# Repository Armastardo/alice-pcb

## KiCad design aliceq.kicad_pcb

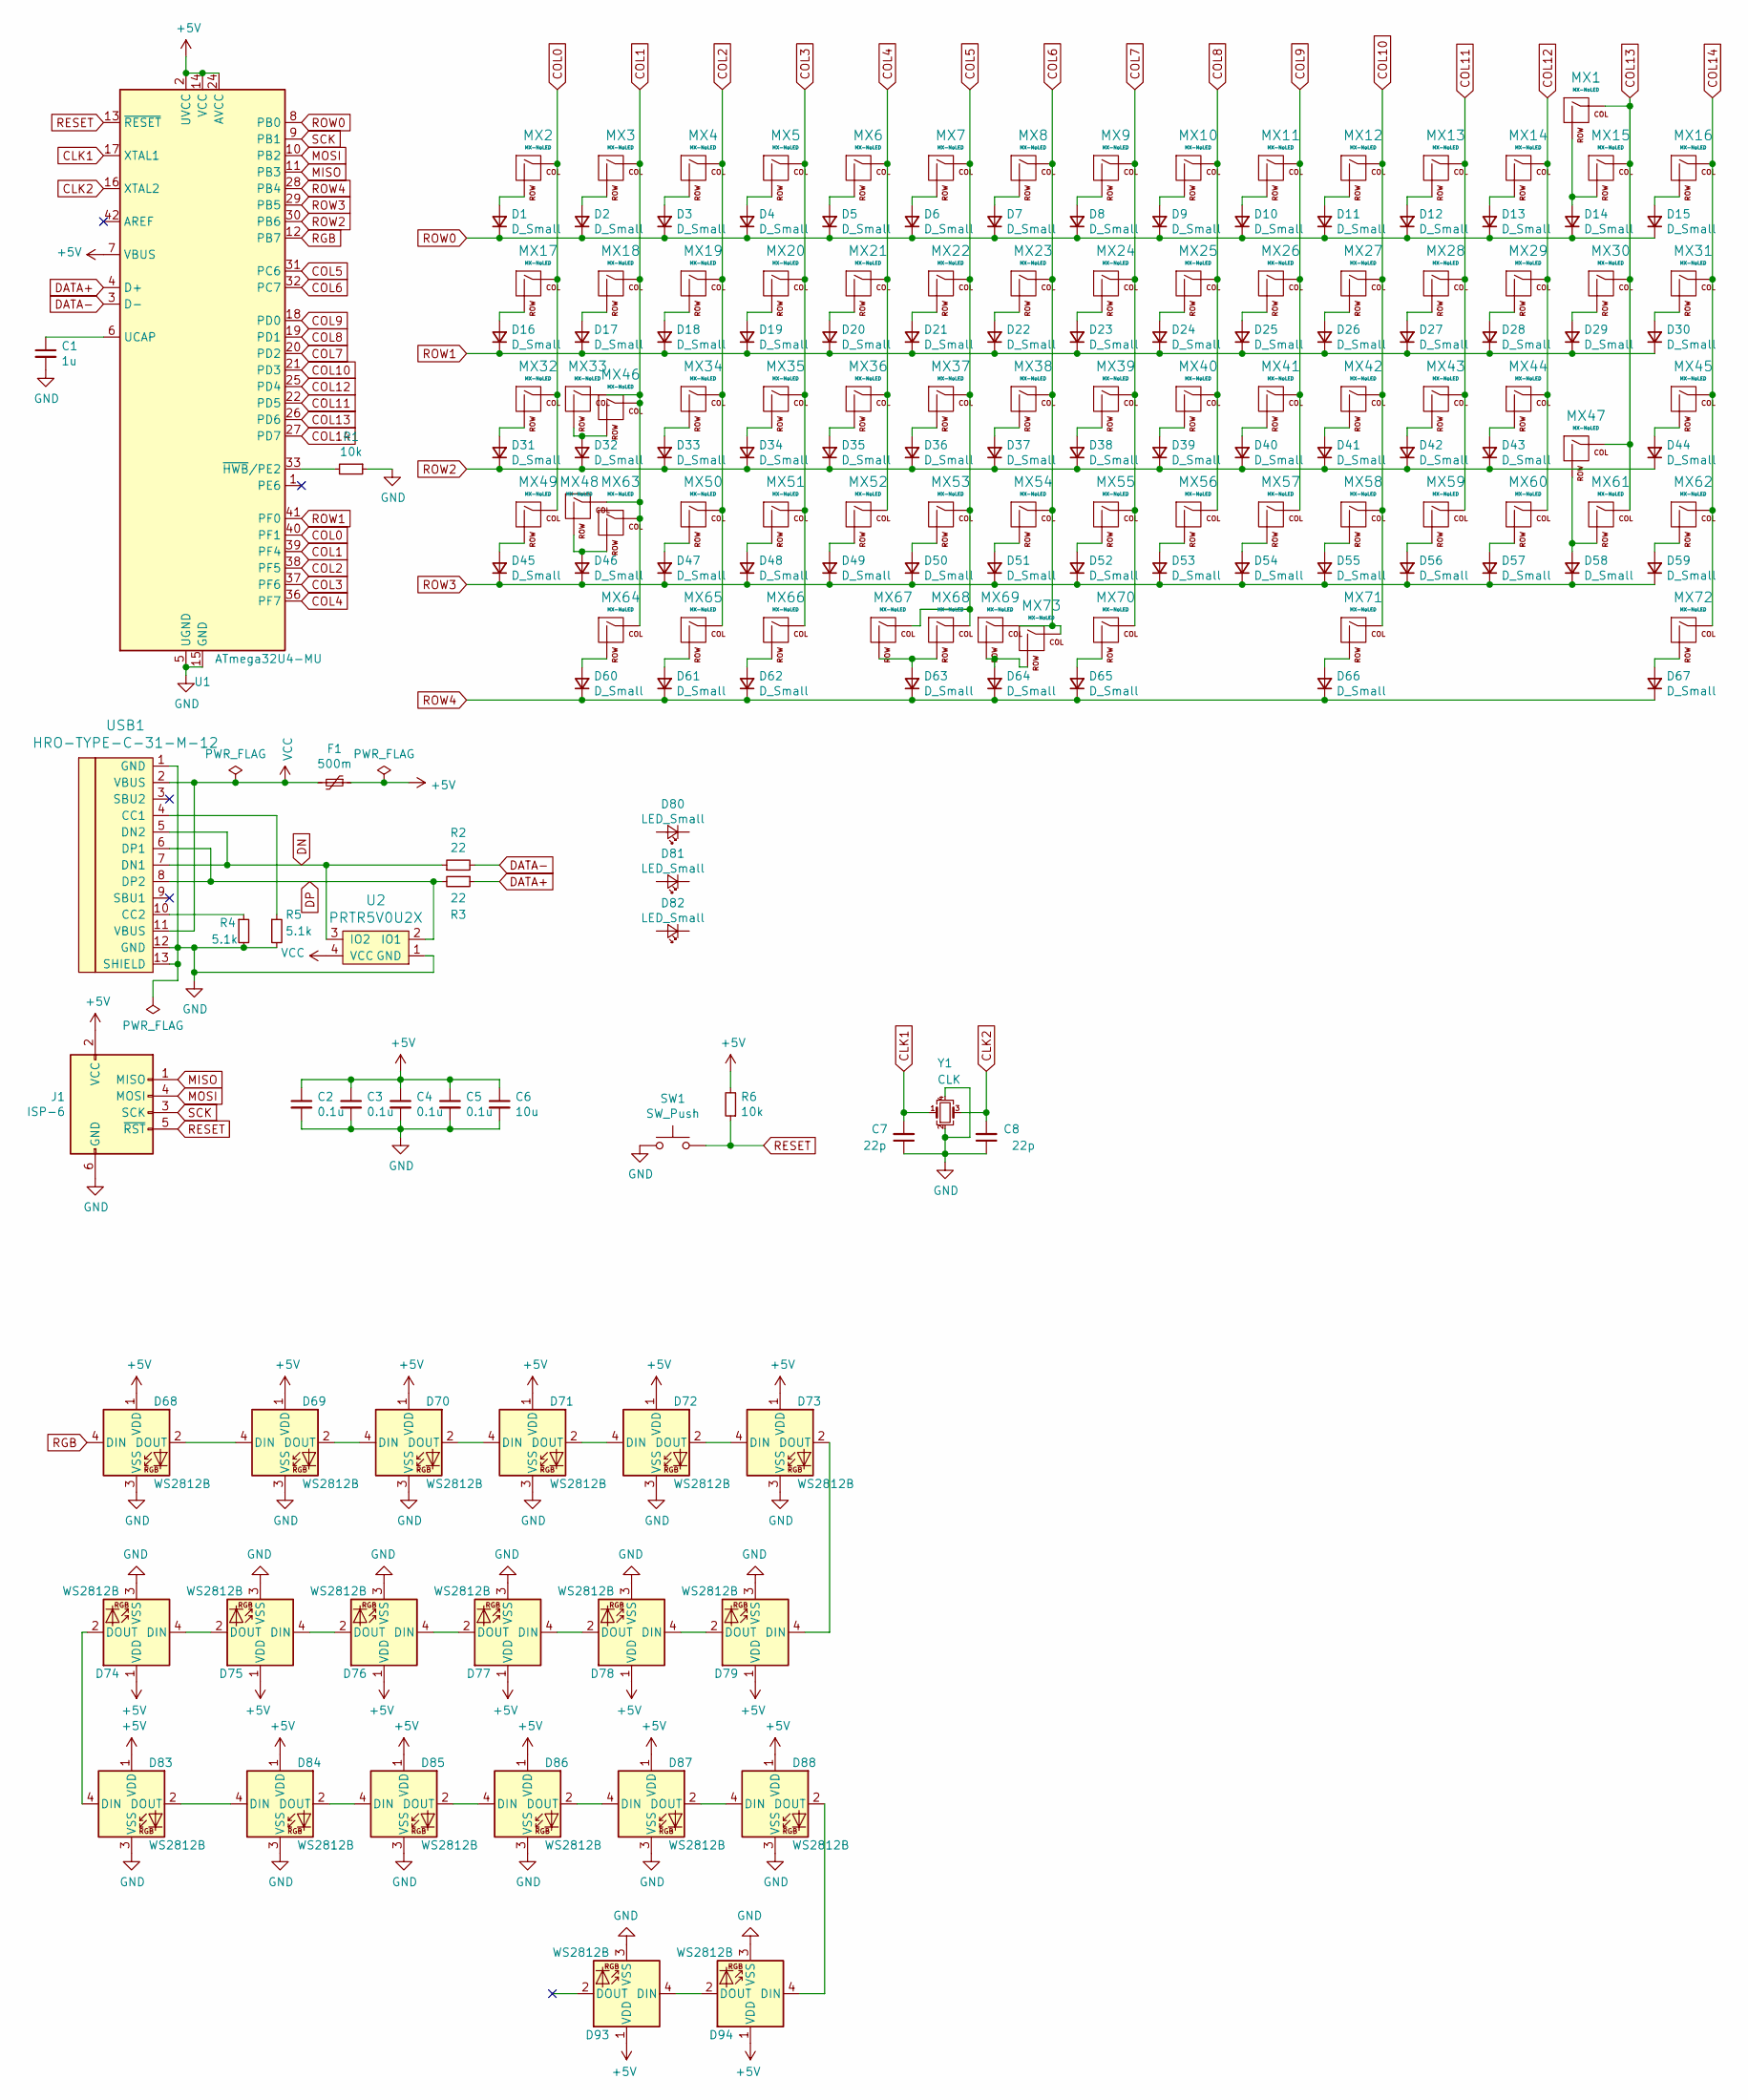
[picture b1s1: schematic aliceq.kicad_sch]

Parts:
C1: 1u; C_0603_1608Metric
C2, C3, C4, C5: 0.1u; C_0603_1608Metric
C6: 10u; C_0603_1608Metric
C7, C8: 22p; C_0805_2012Metric_Pad1.15x1.40mm_HandSolder
D1, D2, D3, D4, D5, D6, D7, D8, D9, D10, D11, D12, D13, D14, D15, D16, D17, D18, D19, D20, D21, D22, D23, D24, D25, D26, D27, D28, D29, D30, D31, D32, D33, D34, D35, D36, D37, D38, D39, D40, D41, D42, D43, D44, D45, D46, D47, D48, D49, D50, D51, D52, D53, D54, D55, D56, D57, D58, D59, D60, D61, D62, D63, D64, D65, D66, D67: D_Small; D_SOD-123; LCSC C2099
D68, D69, D70, D71, D72, D73, D74, D75, D76, D77, D78, D79, D83, D84, D85, D86, D87, D88, D93, D94: WS2812B; LED_WS2812B_PLCC4_5.0x5.0mm_P3.2mm
D80, D81, D82: LED_Small; LED_D1.8mm_W3.3mm_H2.4mm
F1: 500m; Fuse_1206_3216Metric_Pad1.42x1.75mm_HandSolder
J1: ISP-6; Reset_Pretty-Mask
MX1: MX-NoLED; MXOnly-2U-NoLED
MX2, MX3, MX4, MX5, MX6, MX7, MX8, MX9, MX10, MX11, MX12, MX13, MX14, MX15, MX16, MX17, MX19, MX20, MX21, MX22, MX23, MX24, MX25, MX26, MX27, MX28, MX29, MX30, MX32, MX33, MX34, MX35, MX36, MX37, MX38, MX39, MX40, MX41, MX42, MX43, MX44, MX49, MX50, MX51, MX52, MX53, MX54, MX55, MX56, MX57, MX58, MX59, MX60, MX62, MX65, MX69: MX-NoLED; MXOnly-1U-NoLED
MX18, MX31, MX64, MX66, MX71, MX72: MX-NoLED; MXOnly-1.5U-NoLED
MX45, MX67: MX-NoLED; MXOnly-2.25U-ReversedStabilizers-NoLED
MX46, MX61: MX-NoLED; MXOnly-1.75U-NoLED
MX47: MX-NoLED; MXOnly-2.75U-NoLED
MX48: MX-NoLED; MXOnly-2.25U-NoLED
MX63, MX73: MX-NoLED; MXOnly-1.25U-NoLED
MX68: MX-NoLED; MXOnly-2U-ReversedStabilizers-NoLED
MX70: MX-NoLED; MXOnly-2.75U-ReversedStabilizers-NoLED
R1, R6: 10k; R_0603_1608Metric
R2, R3: 22; R_0603_1608Metric
R4, R5: 5.1k; R_0603_1608Metric
SW1: SW_Push; SW_SPST_SKQG_WithStem
U1: ATmega32U4-MU; QFN-44-1EP_7x7mm_P0.5mm_EP5.15x5.15mm
U2: PRTR5V0U2X; SOT143B
USB1: HRO-TYPE-C-31-M-12; HRO-TYPE-C-31-M-12-Assembly
Y1: CLK; Crystal_SMD_3225-4Pin_3.2x2.5mm

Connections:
+5V: C2.1, C3.1, C4.1, C5.1, C6.1, D68.1 (VDD), D69.1 (VDD), D70.1 (VDD), D71.1 (VDD), D72.1 (VDD), D73.1 (VDD), D74.1 (VDD), D75.1 (VDD), D76.1 (VDD), D77.1 (VDD), D78.1 (VDD), D79.1 (VDD), D83.1 (VDD), D84.1 (VDD), D85.1 (VDD), D86.1 (VDD), D87.1 (VDD), D88.1 (VDD), D93.1 (VDD), D94.1 (VDD), F1.1, J1.2 (VCC), R6.2, U1.2 (UVCC), U1.7 (VBUS), U1.14 (VCC), U1.24 (AVCC), U1.34 (VCC), U1.44 (AVCC)
CLK1: C7.2, U1.17 (XTAL1), Y1.1
CLK2: C8.2, U1.16 (XTAL2), Y1.3
COL0: MX2.1 (COL), MX17.1 (COL), MX32.1 (COL), MX49.1 (COL), U1.40 (PF1)
COL1: MX3.1 (COL), MX18.1 (COL), MX33.1 (COL), MX46.1 (COL), MX48.1 (COL), MX63.1 (COL), MX64.1 (COL), U1.39 (PF4)
COL2: MX4.1 (COL), MX19.1 (COL), MX34.1 (COL), MX50.1 (COL), MX65.1 (COL), U1.38 (PF5)
COL3: MX5.1 (COL), MX20.1 (COL), MX35.1 (COL), MX51.1 (COL), MX66.1 (COL), U1.37 (PF6)
COL4: MX6.1 (COL), MX21.1 (COL), MX36.1 (COL), MX52.1 (COL), U1.36 (PF7)
COL5: MX7.1 (COL), MX22.1 (COL), MX37.1 (COL), MX53.1 (COL), MX67.1 (COL), MX68.1 (COL), U1.31 (PC6)
COL6: MX8.1 (COL), MX23.1 (COL), MX38.1 (COL), MX54.1 (COL), MX69.1 (COL), MX73.1 (COL), U1.32 (PC7)
COL7: MX9.1 (COL), MX24.1 (COL), MX39.1 (COL), MX55.1 (COL), MX70.1 (COL), U1.20 (PD2)
COL8: MX10.1 (COL), MX25.1 (COL), MX40.1 (COL), MX56.1 (COL), U1.19 (PD1)
COL9: MX11.1 (COL), MX26.1 (COL), MX41.1 (COL), MX57.1 (COL), U1.18 (PD0)
COL10: MX12.1 (COL), MX27.1 (COL), MX42.1 (COL), MX58.1 (COL), MX71.1 (COL), U1.21 (PD3)
COL11: MX13.1 (COL), MX28.1 (COL), MX43.1 (COL), MX59.1 (COL), U1.22 (PD5)
COL12: MX14.1 (COL), MX29.1 (COL), MX44.1 (COL), MX60.1 (COL), U1.25 (PD4)
COL13: MX1.1 (COL), MX15.1 (COL), MX30.1 (COL), MX47.1 (COL), MX61.1 (COL), U1.26 (PD6)
COL14: MX16.1 (COL), MX31.1 (COL), MX45.1 (COL), MX62.1 (COL), MX72.1 (COL), U1.27 (PD7)
DATA+: R3.1, U1.4 (D+)
DATA-: R2.2, U1.3 (D-)
DN: R2.1, U2.3 (IO2), USB1.5 (DN2), USB1.7 (DN1)
DP: R3.2, U2.2 (IO1), USB1.6 (DP1), USB1.8 (DP2)
GND: C1.2, C2.2, C3.2, C4.2, C5.2, C6.2, C7.1, C8.1, D68.3 (VSS), D69.3 (VSS), D70.3 (VSS), D71.3 (VSS), D72.3 (VSS), D73.3 (VSS), D74.3 (VSS), D75.3 (VSS), D76.3 (VSS), D77.3 (VSS), D78.3 (VSS), D79.3 (VSS), D83.3 (VSS), D84.3 (VSS), D85.3 (VSS), D86.3 (VSS), D87.3 (VSS), D88.3 (VSS), D93.3 (VSS), D94.3 (VSS), J1.6 (GND), R1.1, R4.2, R5.2, SW1.1, U1.5 (UGND), U1.15 (GND), U1.23 (GND), U1.35 (GND), U1.43 (GND), U2.1 (GND), USB1.1 (GND), USB1.12 (GND), USB1.13 (SHIELD), Y1.2, Y1.4
MISO: J1.1 (MISO), U1.11 (PB3)
MOSI: J1.4 (MOSI), U1.10 (PB2)
unnamed: C1.1, U1.6 (UCAP)
unnamed: D1.2 (A), MX2.2 (ROW)
unnamed: D2.2 (A), MX3.2 (ROW)
unnamed: D3.2 (A), MX4.2 (ROW)
unnamed: D4.2 (A), MX5.2 (ROW)
unnamed: D5.2 (A), MX6.2 (ROW)
unnamed: D6.2 (A), MX7.2 (ROW)
unnamed: D7.2 (A), MX8.2 (ROW)
unnamed: D8.2 (A), MX9.2 (ROW)
unnamed: D9.2 (A), MX10.2 (ROW)
unnamed: D10.2 (A), MX11.2 (ROW)
unnamed: D11.2 (A), MX12.2 (ROW)
unnamed: D12.2 (A), MX13.2 (ROW)
unnamed: D13.2 (A), MX14.2 (ROW)
unnamed: D14.2 (A), MX1.2 (ROW), MX15.2 (ROW)
unnamed: D15.2 (A), MX16.2 (ROW)
unnamed: D16.2 (A), MX17.2 (ROW)
unnamed: D17.2 (A), MX18.2 (ROW)
unnamed: D18.2 (A), MX19.2 (ROW)
unnamed: D19.2 (A), MX20.2 (ROW)
unnamed: D20.2 (A), MX21.2 (ROW)
unnamed: D21.2 (A), MX22.2 (ROW)
unnamed: D22.2 (A), MX23.2 (ROW)
unnamed: D23.2 (A), MX24.2 (ROW)
unnamed: D24.2 (A), MX25.2 (ROW)
unnamed: D25.2 (A), MX26.2 (ROW)
unnamed: D26.2 (A), MX27.2 (ROW)
unnamed: D27.2 (A), MX28.2 (ROW)
unnamed: D28.2 (A), MX29.2 (ROW)
unnamed: D29.2 (A), MX30.2 (ROW)
unnamed: D30.2 (A), MX31.2 (ROW)
unnamed: D31.2 (A), MX32.2 (ROW)
unnamed: D32.2 (A), MX33.2 (ROW), MX46.2 (ROW)
unnamed: D33.2 (A), MX34.2 (ROW)
unnamed: D34.2 (A), MX35.2 (ROW)
unnamed: D35.2 (A), MX36.2 (ROW)
unnamed: D36.2 (A), MX37.2 (ROW)
unnamed: D37.2 (A), MX38.2 (ROW)
unnamed: D38.2 (A), MX39.2 (ROW)
unnamed: D39.2 (A), MX40.2 (ROW)
unnamed: D40.2 (A), MX41.2 (ROW)
unnamed: D41.2 (A), MX42.2 (ROW)
unnamed: D42.2 (A), MX43.2 (ROW)
unnamed: D43.2 (A), MX44.2 (ROW)
unnamed: D44.2 (A), MX45.2 (ROW)
unnamed: D45.2 (A), MX49.2 (ROW)
unnamed: D46.2 (A), MX48.2 (ROW), MX63.2 (ROW)
unnamed: D47.2 (A), MX50.2 (ROW)
unnamed: D48.2 (A), MX51.2 (ROW)
unnamed: D49.2 (A), MX52.2 (ROW)
unnamed: D50.2 (A), MX53.2 (ROW)
unnamed: D51.2 (A), MX54.2 (ROW)
unnamed: D52.2 (A), MX55.2 (ROW)
unnamed: D53.2 (A), MX56.2 (ROW)
unnamed: D54.2 (A), MX57.2 (ROW)
unnamed: D55.2 (A), MX58.2 (ROW)
unnamed: D56.2 (A), MX59.2 (ROW)
unnamed: D57.2 (A), MX60.2 (ROW)
unnamed: D58.2 (A), MX47.2 (ROW), MX61.2 (ROW)
unnamed: D59.2 (A), MX62.2 (ROW)
unnamed: D60.2 (A), MX64.2 (ROW)
unnamed: D61.2 (A), MX65.2 (ROW)
unnamed: D62.2 (A), MX66.2 (ROW)
unnamed: D63.2 (A), MX67.2 (ROW), MX68.2 (ROW)
unnamed: D64.2 (A), MX69.2 (ROW), MX73.2 (ROW)
unnamed: D65.2 (A), MX70.2 (ROW)
unnamed: D66.2 (A), MX71.2 (ROW)
unnamed: D67.2 (A), MX72.2 (ROW)
unnamed: D68.2 (DOUT), D69.4 (DIN)
unnamed: D69.2 (DOUT), D70.4 (DIN)
unnamed: D70.2 (DOUT), D71.4 (DIN)
unnamed: D71.2 (DOUT), D72.4 (DIN)
unnamed: D72.2 (DOUT), D73.4 (DIN)
unnamed: D73.2 (DOUT), D79.4 (DIN)
unnamed: D74.2 (DOUT), D83.4 (DIN)
unnamed: D74.4 (DIN), D75.2 (DOUT)
unnamed: D75.4 (DIN), D76.2 (DOUT)
unnamed: D76.4 (DIN), D77.2 (DOUT)
unnamed: D77.4 (DIN), D78.2 (DOUT)
unnamed: D78.4 (DIN), D79.2 (DOUT)
unnamed: D83.2 (DOUT), D84.4 (DIN)
unnamed: D84.2 (DOUT), D85.4 (DIN)
unnamed: D85.2 (DOUT), D86.4 (DIN)
unnamed: D86.2 (DOUT), D87.4 (DIN)
unnamed: D87.2 (DOUT), D88.4 (DIN)
unnamed: D88.2 (DOUT), D94.4 (DIN)
unnamed: D93.4 (DIN), D94.2 (DOUT)
unnamed: R1.2, U1.33 (~HWB~/PE2)
unnamed: R4.1, USB1.10 (CC2)
unnamed: R5.1, USB1.4 (CC1)
RESET: J1.5 (~RST), R6.1, SW1.2, U1.13 (~RESET)
RGB: D68.4 (DIN), U1.12 (PB7)
ROW0: D1.1 (K), D2.1 (K), D3.1 (K), D4.1 (K), D5.1 (K), D6.1 (K), D7.1 (K), D8.1 (K), D9.1 (K), D10.1 (K), D11.1 (K), D12.1 (K), D13.1 (K), D14.1 (K), D15.1 (K), U1.8 (PB0)
ROW1: D16.1 (K), D17.1 (K), D18.1 (K), D19.1 (K), D20.1 (K), D21.1 (K), D22.1 (K), D23.1 (K), D24.1 (K), D25.1 (K), D26.1 (K), D27.1 (K), D28.1 (K), D29.1 (K), D30.1 (K), U1.41 (PF0)
ROW2: D31.1 (K), D32.1 (K), D33.1 (K), D34.1 (K), D35.1 (K), D36.1 (K), D37.1 (K), D38.1 (K), D39.1 (K), D40.1 (K), D41.1 (K), D42.1 (K), D43.1 (K), D44.1 (K), U1.30 (PB6)
ROW3: D45.1 (K), D46.1 (K), D47.1 (K), D48.1 (K), D49.1 (K), D50.1 (K), D51.1 (K), D52.1 (K), D53.1 (K), D54.1 (K), D55.1 (K), D56.1 (K), D57.1 (K), D58.1 (K), D59.1 (K), U1.29 (PB5)
ROW4: D60.1 (K), D61.1 (K), D62.1 (K), D63.1 (K), D64.1 (K), D65.1 (K), D66.1 (K), D67.1 (K), U1.28 (PB4)
SCK: J1.3 (SCK), U1.9 (PB1)
VCC: F1.2, U2.4 (VCC), USB1.2 (VBUS), USB1.11 (VBUS)

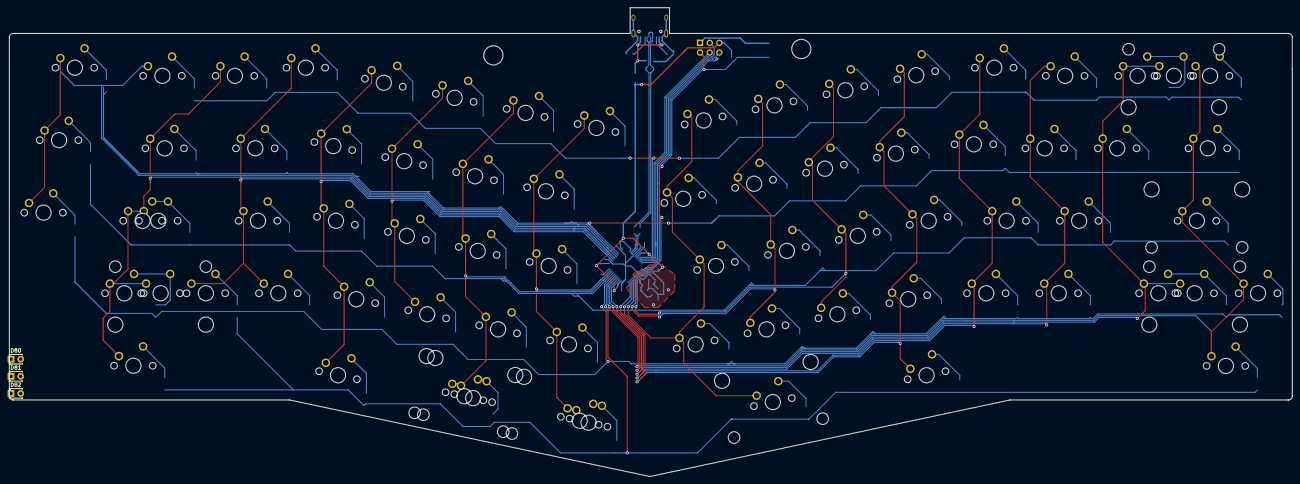
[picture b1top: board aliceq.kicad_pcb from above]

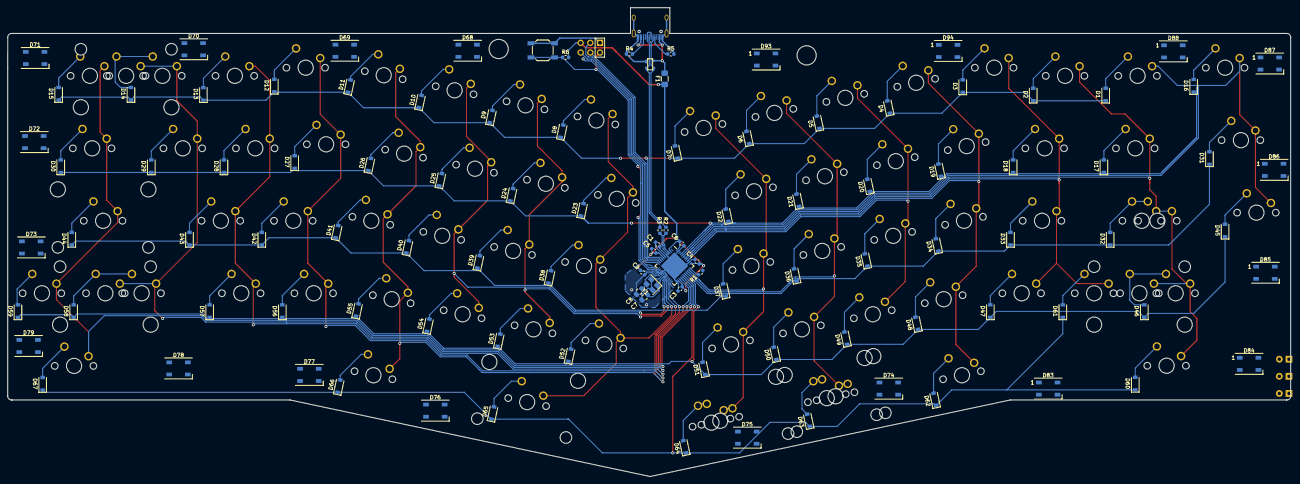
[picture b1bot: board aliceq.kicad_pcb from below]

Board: 2 copper layers, 337.2 x 123.2 mm, 184 parts (108 on the bottom side), 124 nets.

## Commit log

2021-04-02 copy pasteado del smallice
2021-04-02 Sobraban un par de archivos
2021-04-04 Antes del ruteo y posicionamiento de partes
2021-04-05 progreso del fin de semana
2021-04-07 Terminado el ruteado, faltan los leds y el RGB
2021-04-10 Probando arte
2021-04-20 Pre-production
2021-04-20 Terminada la conversión a AU
2021-07-17 hotswap done
2021-08-04 kicad dumdum changes
2021-08-05 hotswap au
2021-11-01 Fixed a weird footprint shennanigang
2021-11-01 beta2
    Fixed the left spacebar, added more sockets for different layout options, added rgb indicators
2021-11-05 More compatibility
2021-11-12 I'm not sure what I did but should be cool
2021-12-31 Fixing hotswap socket positioning
